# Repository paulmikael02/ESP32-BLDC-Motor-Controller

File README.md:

# ESP32-Based BLDC Motor Controller (Firmware & Hardware)

***FI** | **[Lue kattava suomenkielinen dokumentaatio tästä](README_FI.md)***

This repository contains the hardware designs (KiCad) and embedded software (ESP-IDF) for a 3-phase brushless DC (BLDC) motor controller.

The project was developed as part of modernizing the educational equipment in the embedded systems laboratory at SeAMK. The old 8-bit ATmega architecture was upgraded to a modern 32-bit ESP32-C6 platform. The new motherboard was designed to directly support the laboratory's legacy analog and digital input/output expansion boards, preserving compatibility with the existing educational environment.

The firmware has been tested with both a small RC car motor and a larger 750W Vevor electric vehicle motor.

## 🚀 Key Features

* **Hardware:** Two-board design separating 3.3V digital logic from high-power electronics.
* **Firmware:** Event-driven C code built using ESP-IDF and FreeRTOS.
* **Motor Control:** 20 kHz hardware PWM with a 1 µs dead-time to protect the MOSFETs.
* **Performance:** Fast, interrupt-driven 6-step commutation optimized in IRAM.

---

## System Architecture

The system consists of two physical printed circuit boards (PCBs) to electrically isolate the sensitive digital logic from the high-current power electronics.

### Architecture Overview

### 1. ESP32 Carrier Board
Contains the ESP32-C6-based microcontroller, decoupling and bulk capacitors, and the necessary filtering for the power supply.

### 2. BLDC Motor Controller
Contains the 3-phase MOSFET inverter bridge, gate drivers, protection diodes, and bulk and decoupling capacitors for the power input.

---

## 🔌 Pinout Mapping

The physical interface between the software (`include/bldc_control.h`) and the hardware is defined as follows:

| Function | ESP32-C6 Pin | Description / Target on Power Stage |
| :--- | :---: | :--- |
| **PWM U_H / U_L** | GPIO 11 / GPIO 10 | Control for U-phase high- and low-side MOSFETs |
| **PWM V_H / V_L** | GPIO 19 / GPIO 7  | Control for V-phase high- and low-side MOSFETs |
| **PWM W_H / W_L** | GPIO 0 / GPIO 6   | Control for W-phase high- and low-side MOSFETs |
| **Hall U / V / W**| GPIO 5 / GPIO 4 / GPIO 18 | Signal inputs from the motor Hall sensors |
| **Potentiometer** | GPIO 3 (ADC1_CH3)  | Analog voltage input (0–3.3 V) |

---

## 💻 Software Structure and Implementation

The software is written in pure C using the **ESP-IDF (v5.x)** environment and **PlatformIO** tools. The implementation utilizes the FreeRTOS real-time operating system. The software is fully event- and interrupt-driven (no blocking delays), which guarantees accurate motor control even at high rotational speeds.

The code is divided into three logical main components:

### 1. Global Header File and API (`include/bldc_control.h`)
Acts as the hardware definition for the entire system and serves as the public application programming interface (API) for motor control parameters and GPIO definitions. It encapsulates internal helper functions and interrupt handlers away from the main program.

**Low-level critical parameters for motor control:**
* **`PWM_RES_HZ` (10 MHz):** The base clock frequency for the MCPWM module.
* **`PWM_PERIOD` (500):** Defines a 20 kHz PWM frequency ($10\text{ MHz} / 500$). The PWM duty cycle is set between 0 and 500 ticks.
* **`DEAD_TIME_TICKS` (10):** Configures a 1-microsecond hardware dead time between the high- and low-side MOSFETs of each phase to prevent short circuits (shoot-through).
* **GPIO Definitions:** Centralized configurations for the input Hall sensors and power stage transistor outputs.

### 2. Motor Control Logic (`src/bldc_control.c`)
Contains all low-level control logic utilizing the hardware interfaces directly:
* **MCPWM & Dead Time:** Generates the 20 kHz PWM signals for the motor phases and monitors the hardware-level dead time.
* **Interrupt-Driven 6-Step Commutation:** The motor Hall sensors are connected to the MCPWM Capture subsystem. A change in the sensor state triggers an immediate hardware interrupt (`hall_sensor_callback`). To maximize execution speed, the actual commutation function (`update_bldc_commutation`) is placed directly in **IRAM memory**. The code fully supports both forward and reverse commutation sequence tables.
* **FreeRTOS Background Task (`potentiometer_task`):** Handles the potentiometer control and ADC channel processing. It simultaneously calculates the real-time rotational speed from the Hall pulse intervals and filters it using a digital low-pass filter (Exponential Moving Average, $\alpha = 0.10$).

### 3. Main Program (`src/main.c`)
Contains the higher-level application logic. Separate test routines have been built into the file for hardware commissioning:
* **`run_hall_sensor_test()`:** Determines and verifies the sequence and state changes (1–6) of the Hall sensors. The power stage is kept off and the shaft is spun by hand. The order is verified via the serial port, and the motor-specific sequence is updated in the driver's table.
* **`run_speed_ramp_test()`:** Performs an automatic PWM acceleration and braking run to verify the operation of the MOSFET bridges without external interference.
* **Normal Operation (`app_main`):** Runs the main program's `while(1)` loop and tests the code-level direction change sequence (`set_motor_direction`) every 5 seconds.

---

## 📊 Telemetry and Data Visualization

The software outputs real-time data to the serial port every 50 ms. The outputs are formatted using the `>variable:value` standard, allowing direct visualization of the data as a real-time graph using, for example, the **Teleplot** VS Code extension or any Serial Plotter.

**Monitored Variables:**
* `Motor_Duty_Ticks`: PWM pulse width (Counter between 0–500)
* `Hall_State`: Latest state of the Hall sensors (Value between 1–6)
* `Motor_RPM`: Filtered rotational speed (RPM, value is negative when reversing)
* `Motor_Direction`: Direction of rotation (1 = forward, 0 = reverse)

---

## 🛠️ Quick Start

This project is built using **PlatformIO** in VS Code.

```bash
# Clone the repository
git clone https://github.com/paulmikael02/ESP32-BLDC-Motor-Controller.git

# Open in VS Code with the PlatformIO extension installed.
# Build and upload the firmware:
pio run -t upload

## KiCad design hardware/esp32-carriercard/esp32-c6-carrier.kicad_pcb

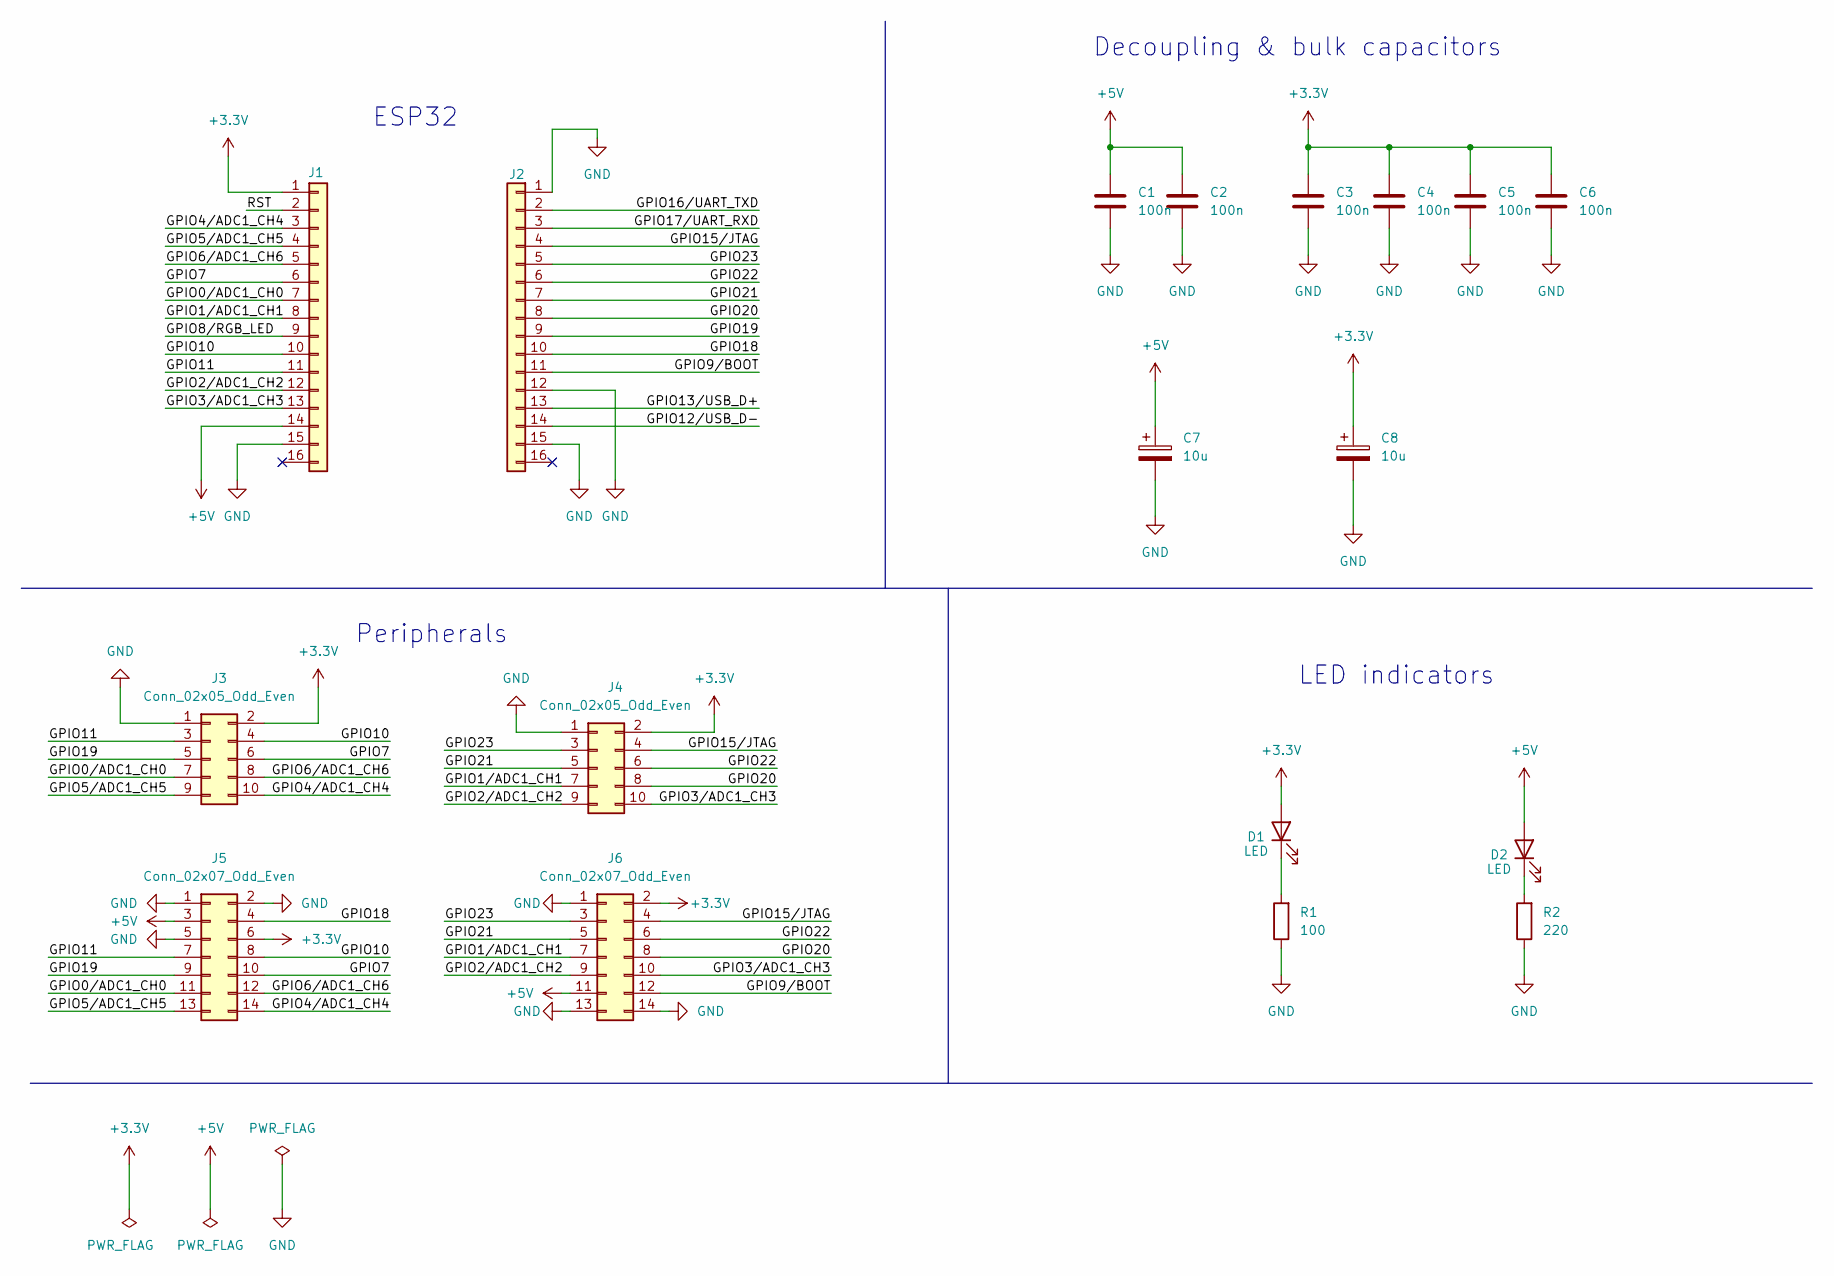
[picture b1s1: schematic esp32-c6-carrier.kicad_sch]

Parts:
C1, C2, C3, C4, C5, C6: 100n; C_Disc_D3.8mm_W2.6mm_P2.50mm
C7, C8: 10u; CP_Radial_D6.3mm_P2.50mm
D1, D2: LED; LED_D5.0mm
J1, J2: Conn_01x16; PinSocket_1x16_P2.54mm_Vertical
J3, J4: Conn_02x05_Odd_Even; IDC-Header_2x05_P2.54mm_Vertical
J5, J6: Conn_02x07_Odd_Even; PinHeader_2x07_P2.54mm_Vertical
R1: 100; R_Axial_DIN0207_L6.3mm_D2.5mm_P7.62mm_Horizontal
R2: 220; R_Axial_DIN0207_L6.3mm_D2.5mm_P7.62mm_Horizontal

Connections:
+3.3V: C3.1, C4.1, C5.1, C6.1, C8.1, D1.2 (A), J1.1, J3.2, J4.2, J5.6, J6.2
+5V: C1.1, C2.1, C7.1, D2.2 (A), J1.14, J5.3, J6.11
/GPIO0/ADC1_CH0: J1.7, J3.7, J5.11
/GPIO1/ADC1_CH1: J1.8, J4.7, J6.7
/GPIO2/ADC1_CH2: J1.12, J4.9, J6.9
/GPIO3/ADC1_CH3: J1.13, J4.10, J6.10
/GPIO4/ADC1_CH4: J1.3, J3.10, J5.14
/GPIO5/ADC1_CH5: J1.4, J3.9, J5.13
/GPIO6/ADC1_CH6: J1.5, J3.8, J5.12
/GPIO7: J1.6, J3.6, J5.10
/GPIO8/RGB_LED: J1.9
/GPIO9/BOOT: J2.11, J6.12
/GPIO10: J1.10, J3.4, J5.8
/GPIO11: J1.11, J3.3, J5.7
/GPIO12/USB_D-: J2.14
/GPIO13/USB_D+: J2.13
/GPIO15/JTAG: J2.4, J4.4, J6.4
/GPIO16/UART_TXD: J2.2
/GPIO17/UART_RXD: J2.3
/GPIO18: J2.10, J5.4
/GPIO19: J2.9, J3.5, J5.9
/GPIO20: J2.8, J4.8, J6.8
/GPIO21: J2.7, J4.5, J6.5
/GPIO22: J2.6, J4.6, J6.6
/GPIO23: J2.5, J4.3, J6.3
/RST: J1.2
GND: C1.2, C2.2, C3.2, C4.2, C5.2, C6.2, C7.2, C8.2, J1.15, J2.1, J2.12, J2.15, J3.1, J4.1, J5.1, J5.2, J5.5, J6.1, J6.13, J6.14, R1.1, R2.1
unnamed: D1.1 (K), R1.2
unnamed: D2.1 (K), R2.2

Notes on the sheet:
LED indicators
ESP32
Peripherals
Decoupling & bulk capacitors

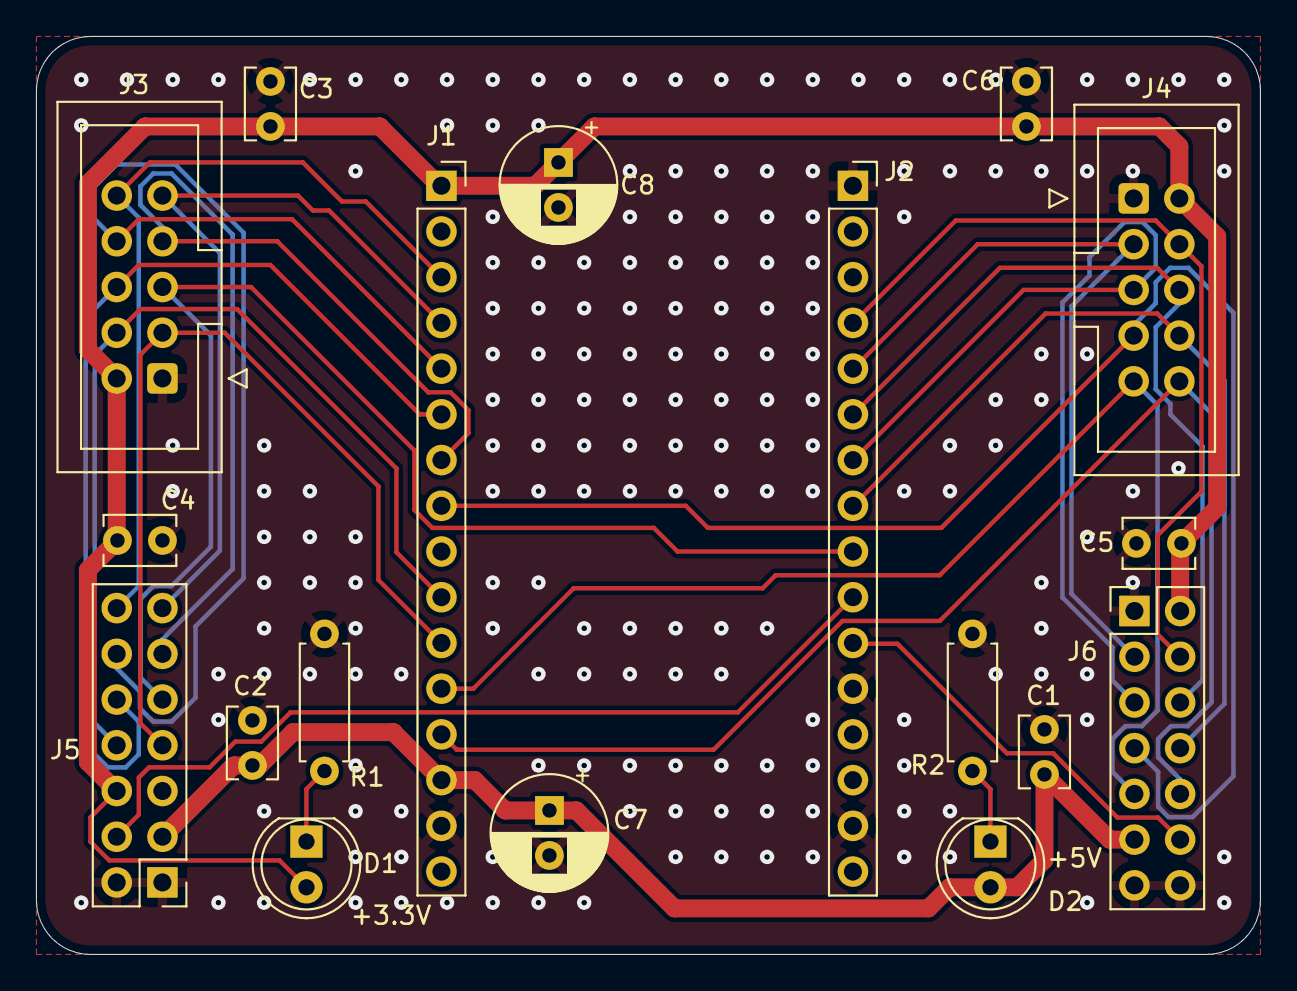
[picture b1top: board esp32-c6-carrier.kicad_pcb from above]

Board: 2 copper layers, 68.0 x 51.0 mm, 18 parts (0 on the bottom side), 23 nets.

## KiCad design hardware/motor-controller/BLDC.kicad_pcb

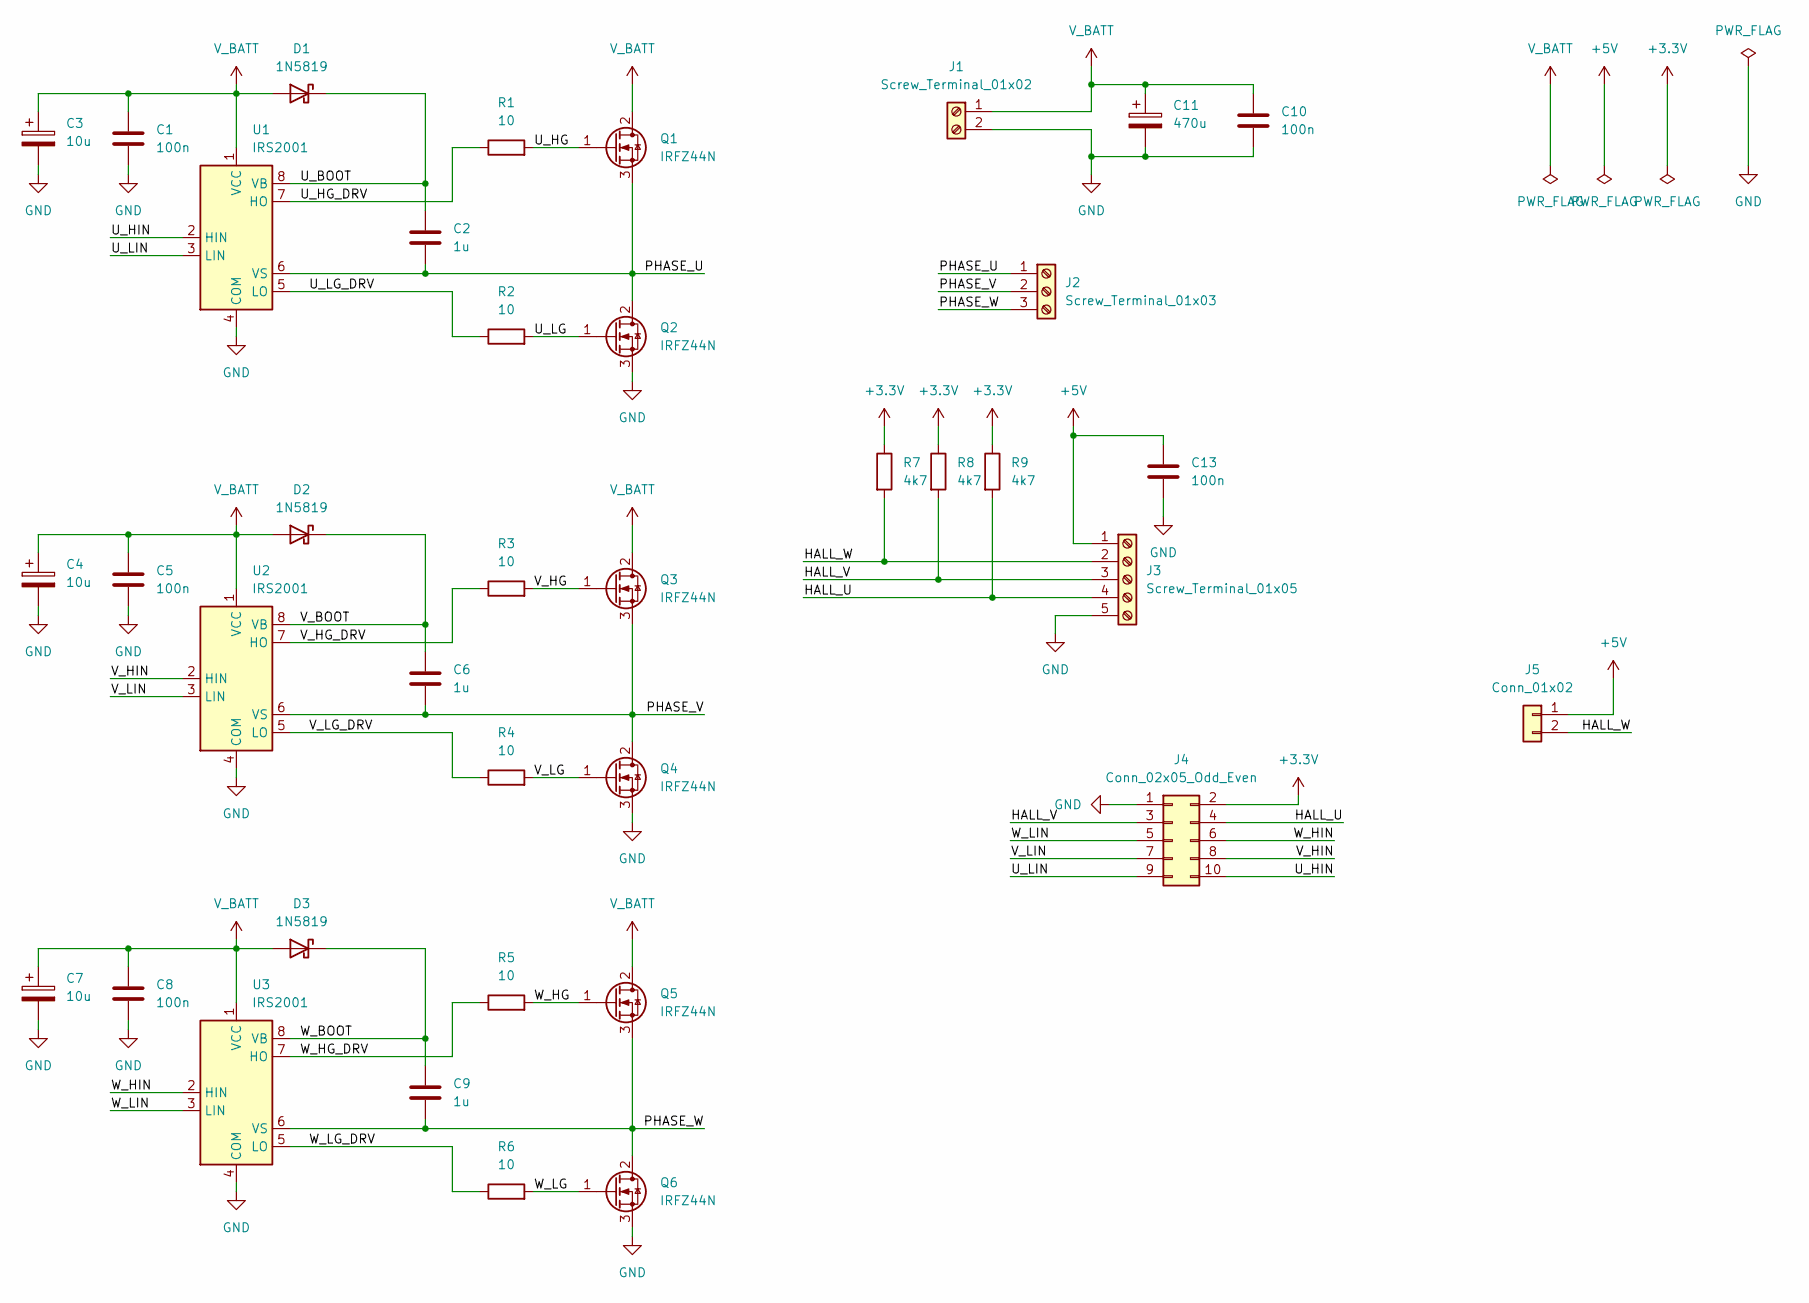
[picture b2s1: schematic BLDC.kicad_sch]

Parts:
C1, C5, C8, C10, C13: 100n; C_Disc_D3.8mm_W2.6mm_P2.50mm
C2, C6, C9: 1u; C_Disc_D5.1mm_W3.2mm_P5.00mm
C3, C4, C7: 10u; CP_Radial_D5.0mm_P2.00mm
C11: 470u; CP_Radial_D10.0mm_P5.00mm
D1, D2, D3: 1N5819; D_DO-41_SOD81_P10.16mm_Horizontal
J1: Screw_Terminal_01x02; TerminalBlock_Phoenix_MKDS-1,5-2-5.08_1x02_P5.08mm_Horizont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
J2: Screw_Terminal_01x03; TerminalBlock_Phoenix_MKDS-1,5-3-5.08_1x03_P5.08mm_Horizont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
J3: Screw_Terminal_01x05; TerminalBlock_Phoenix_MPT-0,5-5-2.54_1x05_P2.54mm_Horizontal
J4: Conn_02x05_Odd_Even; IDC-Header_2x05_P2.54mm_Vertical
J5: Conn_01x02; PinHeader_1x02_P2.54mm_Vertical
Q1, Q2, Q3, Q4, Q5, Q6: IRFZ44N; TO-220-3_Vertical
R1, R2, R3, R4, R5, R6: 10; R_Axial_DIN0207_L6.3mm_D2.5mm_P10.16mm_Horizontal
R7, R8, R9: 4k7; R_Axial_DIN0207_L6.3mm_D2.5mm_P15.24mm_Horizontal
U1, U2, U3: IRS2001; DIP-8_W7.62mm_Socket

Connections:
+3.3V: J4.2, R7.1, R8.1, R9.1
+5V: C13.1, J3.1, J5.1
/HALL_U: J3.4, J4.4, R9.2
/HALL_V: J3.3, J4.3, R8.2
/HALL_W: J3.2, J5.2, R7.2
/PHASE_U: C2.2, J2.1, Q1.3 (S), Q2.2 (D), U1.6 (VS)
/PHASE_V: C6.2, J2.2, Q3.3 (S), Q4.2 (D), U2.6 (VS)
/PHASE_W: C9.2, J2.3, Q5.3 (S), Q6.2 (D), U3.6 (VS)
/U_BOOT: C2.1, D1.1 (K), U1.8 (VB)
/U_HG: Q1.1 (G), R1.2
/U_HG_DRV: R1.1, U1.7 (HO)
/U_HIN: J4.10, U1.2 (HIN)
/U_LG: Q2.1 (G), R2.2
/U_LG_DRV: R2.1, U1.5 (LO)
/U_LIN: J4.9, U1.3 (LIN)
/V_BOOT: C6.1, D2.1 (K), U2.8 (VB)
/V_HG: Q3.1 (G), R3.2
/V_HG_DRV: R3.1, U2.7 (HO)
/V_HIN: J4.8, U2.2 (HIN)
/V_LG: Q4.1 (G), R4.2
/V_LG_DRV: R4.1, U2.5 (LO)
/V_LIN: J4.7, U2.3 (LIN)
/W_BOOT: C9.1, D3.1 (K), U3.8 (VB)
/W_HG: Q5.1 (G), R5.2
/W_HG_DRV: R5.1, U3.7 (HO)
/W_HIN: J4.6, U3.2 (HIN)
/W_LG: Q6.1 (G), R6.2
/W_LG_DRV: R6.1, U3.5 (LO)
/W_LIN: J4.5, U3.3 (LIN)
GND: C1.2, C3.2, C4.2, C5.2, C7.2, C8.2, C10.2, C11.2, C13.2, J1.2, J3.5, J4.1, Q2.3 (S), Q4.3 (S), Q6.3 (S), U1.4 (COM), U2.4 (COM), U3.4 (COM)
V_BATT: C1.1, C3.1, C4.1, C5.1, C7.1, C8.1, C10.1, C11.1, D1.2 (A), D2.2 (A), D3.2 (A), J1.1, Q1.2 (D), Q3.2 (D), Q5.2 (D), U1.1 (VCC), U2.1 (VCC), U3.1 (VCC)

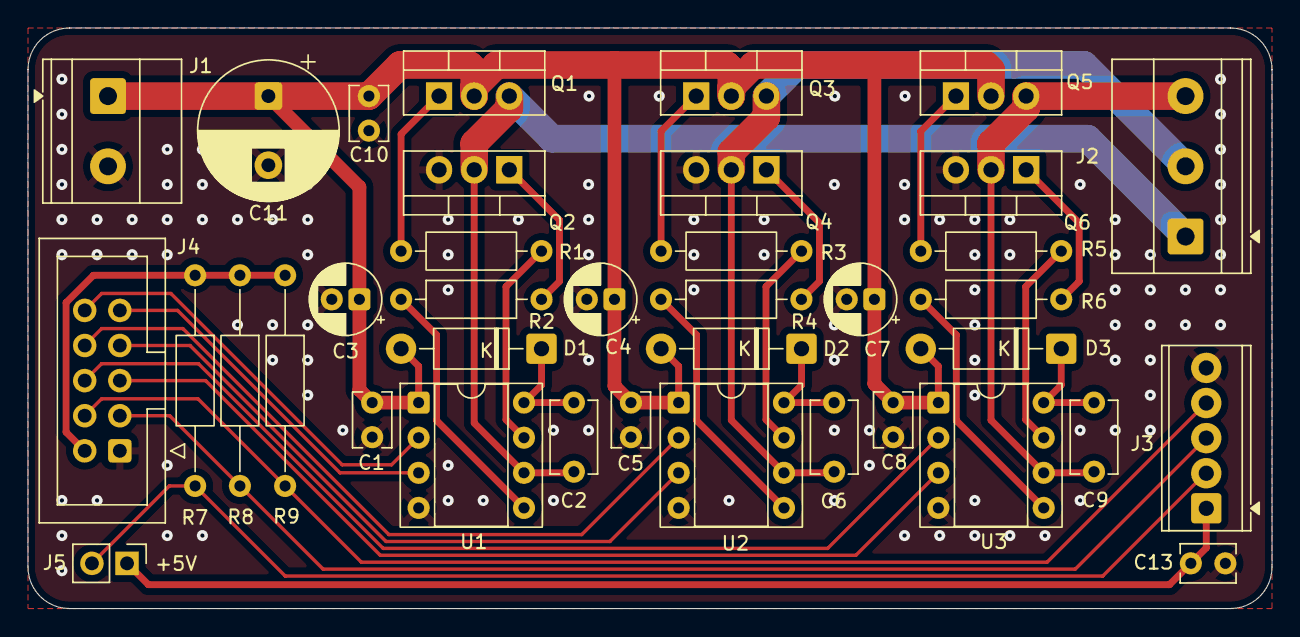
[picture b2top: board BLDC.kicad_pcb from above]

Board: 2 copper layers, 90.0 x 42.0 mm, 38 parts (0 on the bottom side), 31 nets.

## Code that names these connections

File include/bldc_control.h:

#ifndef BLDC_CONTROL_H
#define BLDC_CONTROL_H

#include <stdint.h>

// --- PIN CONFIGURATIONS ---
#define PIN_U_H 11
#define PIN_U_L 10
#define PIN_V_H 19
#define PIN_V_L 7
#define PIN_W_H 0
#define PIN_W_L 6
 
#define PIN_HALL_U 5
#define PIN_HALL_V 4
#define PIN_HALL_W 18

#define PIN_POTENTIOMETER 3
#define ADC_POT_CHANNEL ADC_CHANNEL_3

// --- SYSTEM PARAMETERS ---
#define PWM_RES_HZ 10000000 // 10 MHz clock for MCPWM module
#define PWM_PERIOD 500      // 20 kHz PWM frequency (10MHz / 500)
#define DEAD_TIME_TICKS 10  // 1 microsecond deadtime delay



// --- PUBLIC FUNCTION DECLARATIONS ---
void init_bldc_pwm(void);
void init_hall_sensors(void);
void init_potentiometer_adc(void);
void bldc_force_initial_commutation(void);
void bldc_start_control_task(void);
void set_motor_speed(uint32_t duty_ticks);
void set_motor_direction(uint8_t direction);

#endif // BLDC_CONTROL_H

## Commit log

2026-06-23 Initial release: ESP32 BLDC Motor Controller firmware and hardware
2026-06-23 Refactor main program to use state machine
